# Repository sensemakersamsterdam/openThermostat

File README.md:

# openThermostat
openThermostat is an Open (source) Thermostat design consisting of both hardware and software which offers basic functionality that can be used as a base for every Maker or DIYer to expand upon.

The current version is implemented as an Arduino shield.

# Getting started
To get started you can either [download everything](https://github.com/sensemakersamsterdam/openThermostat/archive/master.zip) in this repository or clone it with `git clone https://github.com/sensemakersamsterdam/openThermostat.git`.
Additionally to get the wiki documentation run `git submodule init` and `git submodule update`.

The repository contains the following files/folders:
* firmware: Arduino sketch to compile and upload to the Arduino the shield is mounted on
  * display_test: Documented code to test the display
  * temp_test: Documented code to test the DS18B20 temperature sensor
* PCB: EAGLE Schematic and PCB layout files as well as exports to PDF and DXF
  * pictures: PNG pictures from the PCB layout and schematic
* wiki: the contents of the openThermostat wiki repository.

More details about building an openThermostatShield and about using the Arduino sketches can be found on the [openThermostatShield wiki page](../../wiki/openThermostatShield).

# Contributing
If you want to contribute feel free to fork the repository, add your changes and send us a pull request. We'd be happy to accept your contributions.
Make your changes in a new branch and please include documentation (using the wiki) for new features and major changes in the pull request.

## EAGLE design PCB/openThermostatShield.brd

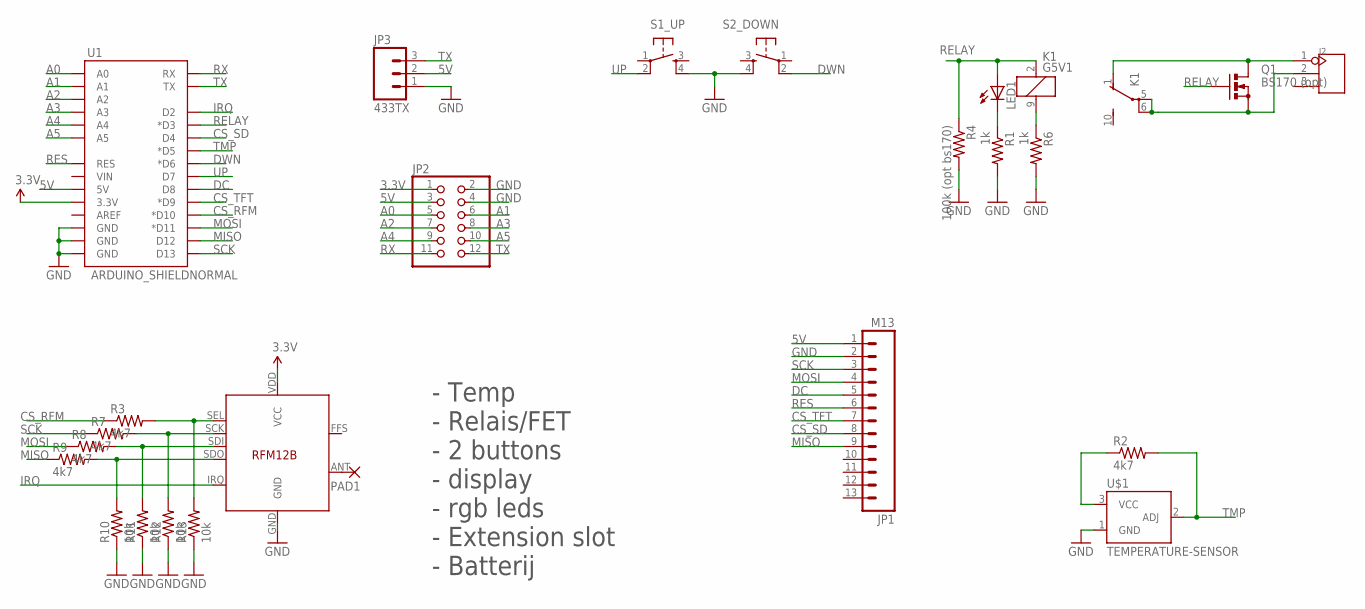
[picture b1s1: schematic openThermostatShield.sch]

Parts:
J2: SCREW-TERMINAL-3P'5.08'; 3P-5.08
JP1: M13; 1X13
JP2: PINHD-2X6/90; 2X06/90
JP3: 433TX; MOLEX-1X3
K1: G5V1
LED1: LED-3MM-NO_SILK; LED3MM-NS
PAD1: 1,6/0,8
Q1: BS170 (opt); SOT54E
R1, R6: 1k; AXIAL-0.3
R2, R3, R7, R8, R9: 4k7; AXIAL-0.3
R4: 100k (opt bs170); AXIAL-0.3
R10, R11, R12, R13: 10k; AXIAL-0.3
S1_UP, S2_DOWN: TAC_SWITCHPTH; TACTILE-PTH
U1: ARDUINO_SHIELDNORMAL; DUEMILANOVE_SHIELD_5X5
U$1: TEMPERATURE-SENSOR; TO-92
U$2: RFM12B

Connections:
3.3V: JP2.1, U1.3.3V, U$2.VDD (VCC)
5V: JP1.1, JP2.3, JP3.2, U1.5V
A0: JP2.5, U1.A0
A1: JP2.6, U1.A1
A2: JP2.7, U1.A2
A3: JP2.8, U1.A3
A4: JP2.9, U1.A4
A5: JP2.10, U1.A5
CS_RFM: R3.P$1 (1), U1.D10 (*D10)
CS_SD: JP1.8, U1.D4
CS_TFT: JP1.7, U1.D9 (*D9)
DC: JP1.5, U1.D8
DWN: S2_DOWN.2, U1.D6 (*D6)
GND: JP1.2, JP2.2, JP2.4, JP3.1, R1.P$2 (2), R4.P$2 (2), R6.P$2 (2), R10.P$1 (1), R11.P$1 (1), R12.P$1 (1), R13.P$1 (1), S1_UP.4, S2_DOWN.4, U1.GND@0 (GND), U1.GND@1 (GND), U1.GND@2 (GND), U$1.1 (GND), U$2.GND
IRQ: U1.D2, U$2.IRQ
MISO: JP1.9, R9.P$1 (1), U1.D12
MOSI: JP1.4, R8.P$1 (1), U1.D11 (*D11)
unnamed: K1.9 (2), R6.P$1 (1)
unnamed: J2.1, K1.1 (O), Q1.D
unnamed: LED1.K (C), R1.P$1 (1)
unnamed: J2.2, K1.5, K1.6, Q1.S
unnamed: R2.P$1 (1), U$1.3 (VCC)
unnamed: PAD1.1, U$2.ANT
unnamed: R9.P$2 (2), R10.P$2 (2), U$2.SDO
unnamed: R8.P$2 (2), R11.P$2 (2), U$2.SDI
unnamed: R7.P$2 (2), R12.P$2 (2), U$2.SCK
unnamed: R3.P$2 (2), R13.P$2 (2), U$2.SEL
RELAY: K1.2 (1), LED1.A, Q1.G, R4.P$1 (1), U1.D3 (*D3)
RES: JP1.6, U1.RES
RX: JP2.11, U1.RX
SCK: JP1.3, R7.P$1 (1), U1.D13
TMP: R2.P$2 (2), U1.D5 (*D5), U$1.2 (ADJ)
TX: JP2.12, JP3.3, U1.TX
UP: S1_UP.2, U1.D7

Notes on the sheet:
- Temp - Relais/FET - 2 buttons - display - rgb leds - Extension slot - Batterij

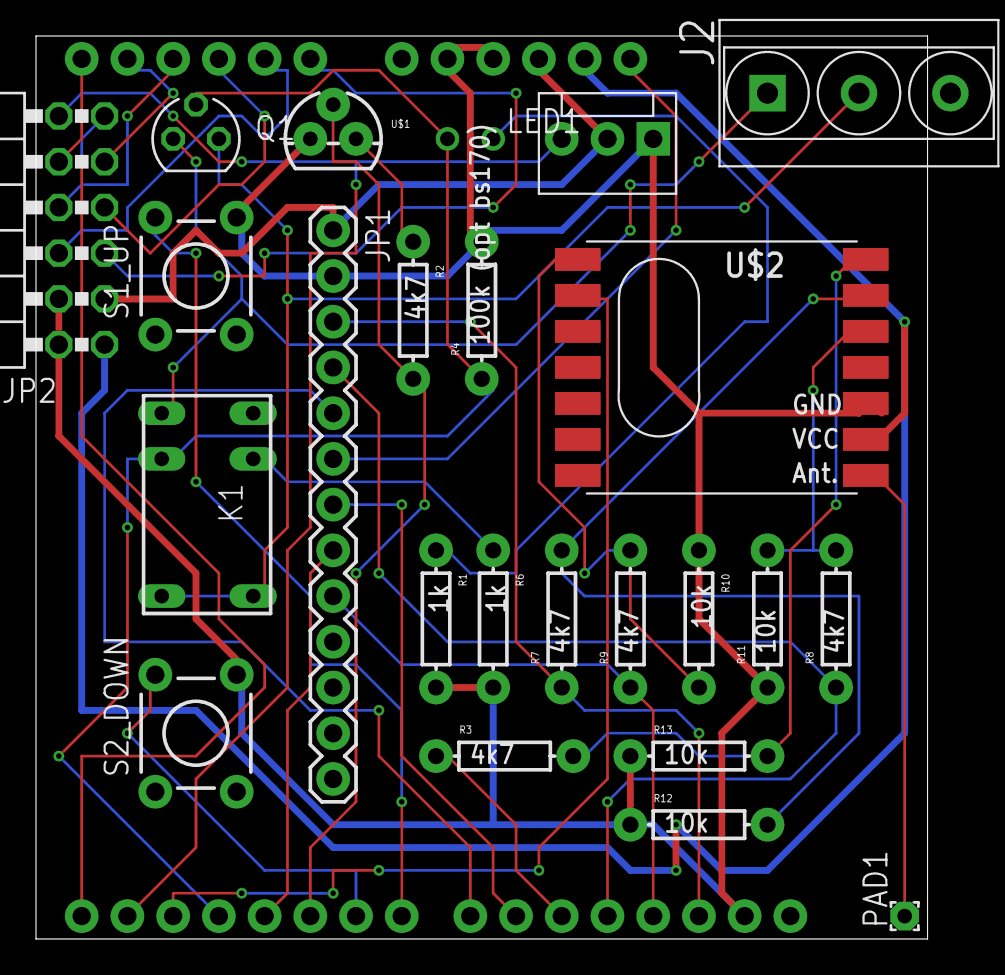
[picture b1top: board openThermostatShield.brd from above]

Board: 2 copper layers, 49.5 x 50.2 mm, 25 parts (0 on the bottom side), 34 nets.

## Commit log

2013-12-20 Add GitHub wiki pages to repo as submodule
2013-12-20 Add files from meetup/dropbox closes #2
2014-04-05 Update display_test.ino
    Added import for Arduino.h to ensure this compiles on OS X with Arduino 1.0.5 IDE
2014-04-05 Added a word document with details on how to solder the board and what other requirements are there in order to compile the test code.
2016-06-22 Add scenario's, brainstorm photo and case options and photo's

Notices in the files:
parts and their libraries:
SparkFun-Boards: Licensing: CC v3.0 Share-Alike You are welcome to use this library for commercial purposes.
